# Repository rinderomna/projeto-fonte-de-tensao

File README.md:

# Trabalho 1 - Projeto de Fonte de Tensão Ajustável
Projeto realizado no primeiro semestre do curso de Bacharelado em Ciências de Computação, para a disciplina '[SSC0180] – Eletrônica para Computação', ministrada pelo professor Eduardo do Valle Simões, da USP de São Carlos.

# Alunos - Grupo 2

| **Nome Completo**              | **N°USP**|
|--------------------------------|----------|
| [Danielle Modesti](https://github.com/danimodesti)               | 12543544 |
| [Hélio Nogueira Cardoso](https://github.com/rinderomna)         | 10310227 | 
| [Raphael David Phillippe Levéque](https://github.com/raphaelleveque)| 12542522 |

# Objetivo
Projetar uma fonte de tensão retificadora, ajustável entre 3V e 12V, com capacidade de 100mA.

# Diagrama da Fonte

[Link para o circuito no Falstad](https://tinyurl.com/yengesgj)

# Escolha de Componentes

| Quantidade  | Componente  | Especificações   | Valor  |
|---|---|---|---|
| 1 | [Transformador](https://produto.mercadolivre.com.br/MLB-1253943633-transformador-trafo-1818v-200ma-bivolt-eletronica-_JM#position=1&search_layout=stack&type=item&tracking_id=167d04df-57da-4808-83a5-ea7012a22afe) |Trafo Bivolt 18+18v 200mA|R$27,99|
| 1 | [Ponte de Diodos](https://www.baudaeletronica.com.br/ponte-retificadora-kbpc1010.html) | Ponte Retificadora KBPC1010 |R$3,67| 
| 1 | [Capacitor](https://produto.mercadolivre.com.br/MLB-1673538375-capacitor-d97-eletrolitico-smd-560uf-25v-emb-10-pcs-_JM?matt_tool=87716990&matt_word=&matt_source=google&matt_campaign_id=12413740998&matt_ad_group_id=119070072438&matt_match_type=&matt_network=g&matt_device=c&matt_creative=500702333978&matt_keyword=&matt_ad_position=&matt_ad_type=pla&matt_merchant_id=109554163&matt_product_id=MLB1673538375&matt_product_partition_id=337120033364&matt_target_id=pla-337120033364&gclid=CjwKCAjwuvmHBhAxEiwAWAYj-Ay7yDPELDOSm39X_i7gBUjtOCS0CwJmOsPk51wYcrQWBM-lYwfB2xoCgIcQAvD_BwE) |560µF, 25V|R$1,10|
| 1 | [LED](https://www.baudaeletronica.com.br/led-de-alto-brilho-10mm-vermelho.html) |Vermelho 3V - 3,3V 30mA|R$0,70|
| 1 | [Diodo Zener](https://www.baudaeletronica.com.br/diodo-zener-1n4743-13v-1w.html) |1N4743 [13V / 1W]|R$0,19|
| 1 | [Potenciômetro](https://www.baudaeletronica.com.br/potenciometro-linear-de-10k-10000.html) |10000Ω|R$1,61|
| 1 | [Resistor 680](https://www.baudaeletronica.com.br/resistor-680r-5-2w.html) |680Ω +/-5%, 2W|R$0,38|
| 1 | [Resistor 1k](https://www.baudaeletronica.com.br/resistor-1k-5-1w.html) |1000Ω +/-5%, 1W|R$0,18|
| 1 | [Resistor 3k9](https://www.baudaeletronica.com.br/resistor-3k9-5-2w.html) |3900Ω +/-5%, 2W|R$0,38|
| Total | | |R$36,20|

# Projeto Esquemático do PCB no Software Eagle

# Vídeos Explicativos
[Vídeo explicando cálculos](https://www.youtube.com/watch?v=foXTuA22R3k)

[Vídeo explicando as etapas](https://www.youtube.com/watch?v=o96vAONC0xM)

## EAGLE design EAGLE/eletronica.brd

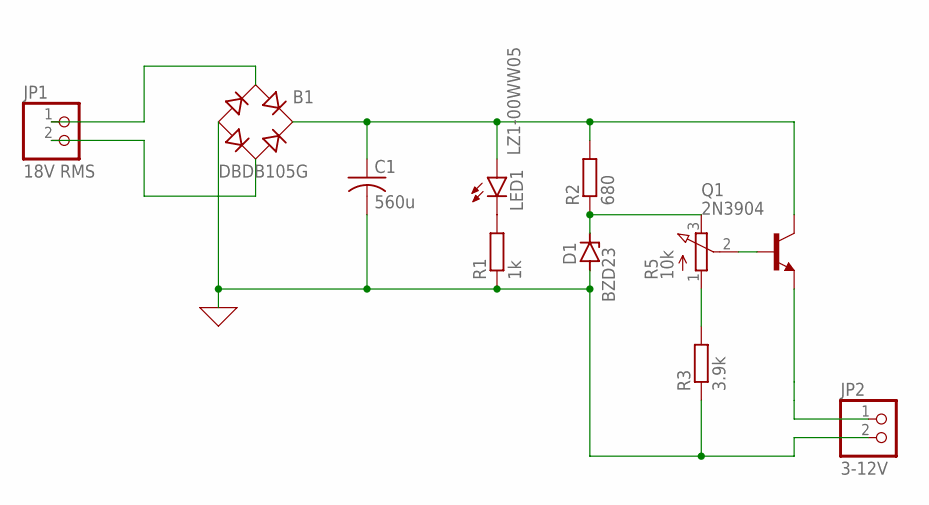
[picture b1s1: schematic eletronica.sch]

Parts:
B1: DBDB105G; DB
C1: 560u; C025-025X050
D1: BZD23; SOD81
JP1: 18V RMS; 1X02
JP2: 3-12V; 1X02
LED1: LZ1-00WW05; LZ1-00WW03
Q1: 2N3904; TO92
R1: 1k; 0204/7
R2: 680; 0204/7
R3: 3.9k; 0204/7
R5: 10k; 3RP/1610N

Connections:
unnamed: B1.AC1, JP1.1
unnamed: B1.AC2, JP1.2
unnamed: B1.-, C1.2, D1.A, JP2.2, R1.1, R3.1
unnamed: B1.+, C1.1, LED1.2 (A), LED1.3 (A), LED1.5 (A), Q1.1 (C), R2.2
unnamed: D1.C, R2.1, R5.3 (E)
unnamed: Q1.2 (B), R5.2 (S)
unnamed: R3.2, R5.1 (A)
unnamed: LED1.1 (C), LED1.4 (C), R1.2

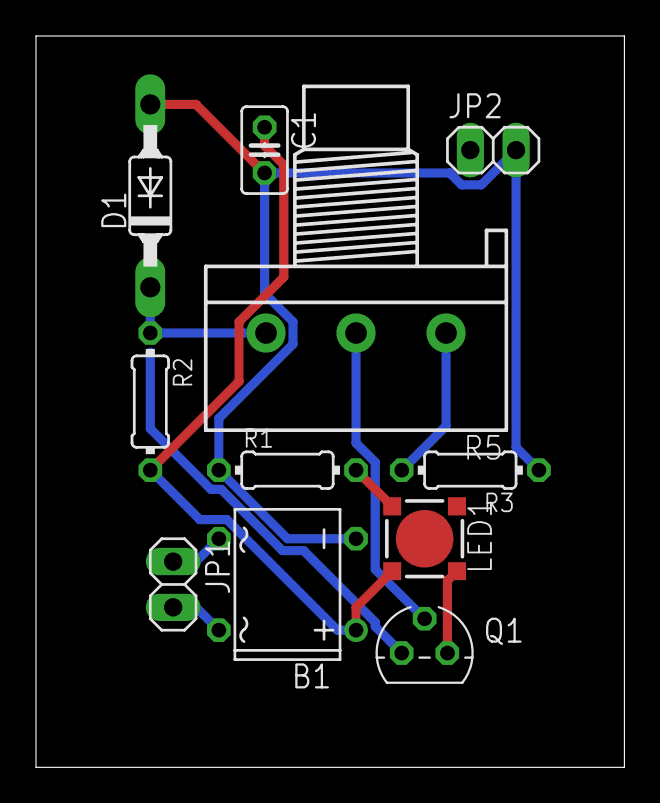
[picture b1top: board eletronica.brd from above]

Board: 2 copper layers, 32.7 x 40.6 mm, 11 parts (0 on the bottom side), 8 nets.

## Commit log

2021-07-26 foto
2021-07-26 estou testando o commit
2021-07-27 esquematicos1
2021-07-27 novo circuito do falstad
2021-07-27 novos arquivos
2021-07-27 new name
2021-07-27 corrigindo imagem
2021-07-27 redimensionamento das imagens
2021-07-27 Adicionando o EAGLE
